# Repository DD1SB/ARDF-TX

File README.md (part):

# ARDF-TX

**Hardware evaluation stage — physical transmitter qualification pending.**

ARDF-TX is a modular open-source transmitter platform for Amateur Radio Direction
Finding (ARDF), with separate 80 m and 2 m RF boards and a common ESP32-S3
controller. Its goals are affordable reproduction, ordinary PCB manufacturing,
autonomous contest timing, optional remote operation and explicit hardware
transmitter interlocks.

**Mini80-SMD is a fourth, independent transmitter family:** a standalone,
low-power 80 m board with its own AVR firmware and protected 1S battery. Its
35 × 35 mm evaluation design operates without the ESP32 controller. Mini80's
sources and manufacturing review are published on `mini80-smd-evaluation`; the
Mini80 links below are pinned to the published review commit so they also work
from `main`, where the experimental hardware files are not included.

The repository contains editable KiCad sources, development history, engineering
decisions, population BOMs, verification tools and revision-specific fabrication
data. The RF designs and M6-L2 controller have independent CAD reviews. The fresh
[M6-L2 final reproduction](docs/M6_L2_FINAL_REPRODUCTION.md) supports **GO for five
controlled bare controller evaluation boards**. Physical qualification and release
for operation remain pending. No PCB has been ordered or tested.

The current RF2M revision is **M5B-E6R2**, with carrier-keyed A2A,
one shared heatsink and instrumented bring-up access. Independent engineering
review found no concrete blocker for **five bare evaluation PCBs**. See the
[E6R2 decision](docs/M5B_E6R2_REVIEW_DECISION.md) and
[final reproduction](docs/M5B_E6R2_FINAL_PUBLICATION.md). Physical RF, thermal
and operational qualification remains **NOT_RUN**. The earlier
[E6](docs/M5B_E6_REVIEW_DECISION.md) and
[E6R1](docs/M5B_E6R1_REVIEW_DECISION.md) HOLD studies remain preserved evidence.
Controller M6-L2 and RF80 are unchanged. No board or stencil has been ordered.

## Hardware architecture

| Module | Current candidate / source commit | PCB | Main functions | Native KiCad project | Engineering review |
| --- | --- | --- | --- | --- | --- |
| Common controller | **M6-L2 — ESP32 external antenna, FoxPro2 compatibility and optional GPIO expansion** / [`89f5a7d`](https://github.com/DD1SB/ARDF-TX/commit/89f5a7df6ccb4dec8fcea10e7c810a9981342ce4); previous baseline [`d94dabd`](https://github.com/DD1SB/ARDF-TX/commit/d94dabd0e40137dc44b2bb94f3707ad4636ca65f) | 100 × 100 mm | External-antenna ESP32-S3, RTC, USB-C, optional LoRa/FoxPro2/GPIO expansion and default-off interlocks | [CTRL.kicad_pro](hardware/controller/CTRL.kicad_pro) | [M6-L2](hardware/controller/review/M6-L2/README.md), previous [M6-L1](hardware/controller/review/M6-L1/README.md) |
| 80 m RF | M4A-V1R1 / [`f86684b`](https://github.com/DD1SB/ARDF-TX/commit/f86684b9ef45eec3ca4ce52edcb62896a847f1d7) | 150 × 110 mm | Si5351, LM5134B, IRF610, Classic/Sprint profiles and independent Foxoring output | [RF80_V1.kicad_pro](hardware/80m/production/RF80_V1.kicad_pro) | [M4A-V1R1](hardware/80m/production/review/M4A-V1R1/README.md) |
| 2 m RF | **M5B-E6R2 — reviewed evaluation candidate** / [`2fff321`](https://github.com/DD1SB/ARDF-TX/commit/2fff32131dd0f7da3c46fef47c04713a55df89d8); historical E5 / [`3b84366`](https://github.com/DD1SB/ARDF-TX/commit/3b84366caa985fac67fbdfbb60c4ede751b3a13e) | 150 × 110 mm | Carrier-keyed A2A, Si5351, PHA-1+, PD54008L-E, unified cooling and independent training output | [RF2M.kicad_pro](hardware/2m/RF2M.kicad_pro) | [E6R2](hardware/2m/review/M5B-E6R2/README.md); preserved [E5](hardware/2m/review/M5B-E5/README.md) |
| Standalone 80 m Mini80 | **M80-E1 hardware / M80-E2 bare-board review** / [hardware `bdac015`][mini80-e1-commit], [review `2bf55b5`][mini80-e2-commit] | **35 × 35 mm**, two layers | ATtiny1616-MNR, Si5351A-B-GT, 74HCT240PW; autonomous MINI50 training / FOX10 candidate; independent battery and fixture | [Mini80.kicad_pro][mini80-project] | [M80-E2: GO for five bare evaluation PCBs][mini80-review] |

The RF80 and RF2M boards share a **140 × 100 mm four-point M3 mounting pattern**.
The controller mounts independently and connects through short keyed IDC cables:
16 pins for RF80, 20 pins for RF2M. Their interfaces must not be interchanged.
RF battery power uses separate connectors, never the IDC cable. Normally only
one band/path transmits at a time.

The common footprint does not establish a qualified enclosure or three-board
stack. Cooling, controller antenna clearance and cable access are described in
the [historical common-enclosure study](docs/M5B_E5_COMMON_ENCLOSURE.md) and
[E6R2 mechanical assembly](docs/M5B_E6R2_MECHANICAL_ASSEMBLY.md). E6R2 places its
cooler below the board, with a protected carrier and independent supports. A
stack with both RF modules remains a physical qualification item.

Mini80 uses its own battery, two M2 mounting holes and six-pad bottom-side pogo
interface. It does not use the shared ESP32 controller, either IDC interface or
the RF80/RF2M mounting pattern.

## Intended operating modes

| Band | Intended modes |
| --- | --- |
| 80 m RF80 | Classic, Sprint, and Foxoring through a separate nominal 10 mW path |
| 2 m RF2M | Classic with genuine sinusoidal A2A amplitude modulation, and an independent very-low-power training path |
| Standalone 80 m Mini80 | Informal Sprint/training with MINI50; continuous FOX10 Foxoring candidate pending calibration and field verification |

For the controller/RF80/RF2M system, the controller contract supports configurable
schedules, Morse identification, Sprint slow/fast groups and spectator/finish-beacon
roles. Simultaneous Sprint
groups operate across a fleet; one station executes its assigned role.
Frequencies and operating profiles are configurable. Continuous beacons need
their own power/endurance model.

RF power, 70–80% AM, ERP and 12 h full / 24 h reduced-power endurance remain
**targets requiring measurement**. Antenna/feed gain, legal frequencies/power
and country/operator authorization must be established separately. IARU event
rules do not grant permission to transmit.

## Standalone 80 m Mini80 transmitter

[Mini80-SMD][mini80-readme] is an autonomous **35 × 35 mm, two-layer** low-power
80 m transmitter inspired by DF1FO's 80mSprintTX. An **ATtiny1616-MNR** controls
the **Si5351A-B-GT** programmable carrier source and **74HCT240PW,118** output
stage. Eight HCT outputs each have their own ballast resistor before the RF
signal is combined and passed through the output low-pass filter. A protected
**1S Li-ion/LiPo battery** supplies onboard **3.0 V logic** and a switched,
nominal 5 V RF supply. Charging is external; no charger is fitted, and the board's
protection circuitry does not replace a protected cell.

![Mini80 native KiCad mechanical rendering][mini80-render]

The rendering includes optional component envelopes; it is not a photograph of
assembled hardware or a statement that every shown matching component is fitted.

The two populations share the same PCB and firmware. Their nominal power
estimates use a **50 Ω reference load**, 3.55 MHz, a 4.95 V RF rail and assumed
HCT output resistance:

| Population | Eight ballast resistors | Calculated nominal RF power | Intended use |
| --- | --- | --- | --- |
| **MINI50** | 8 × 100 Ω | **47.4 mW into 50 Ω** | Informal Sprint/training only; below the official Sprint 0.3–1 W output requirement and not competition-compliant Sprint output |
| **FOX10** | 8 × 560 Ω | **10.16 mW into 50 Ω** | Foxoring candidate pending conducted-power calibration, real-antenna tuning and field verification |

Optional antenna matching populations provide impedance transformation and
selectable loading for wire training antennas. A short Foxoring antenna needs
its own selected coupling/matching setup; one population is not assumed optimal
for both. The FOX10 first-article bench population bypasses the optional matching
bank; testing requires a characterized 50 Ω dummy load. RF power, runtime estimates and antenna
models are **calculations, not physical measurements**. Adjusting conducted
power alone does not establish the required Foxoring field range.

One universal AVR firmware image supports per-unit settings for carrier
frequencies from **3.510–3.600 MHz**, role, Morse identifier, keying speed,
physical power profile, schedule and calibration. The twelve Sprint roles are
five slow and five fast transmitters, each using **MOE, MOI, MOS, MOH, MO5**,
plus spectator **S** and finish/training **MO**. Default group speeds are 10/15
WPM. The slotted roles use nominal 12-second windows in a 60-second cycle;
continuous Foxoring identifiers and independent continuous S/MO modes are also
supported. The low-power MO training role does not cover a normal-power
competition Foxoring finish beacon.

The AVR runs autonomous scheduling, Morse generation, separate carrier/timing
calibration and synchronized starting. Persistent configuration does not retain
an armed state; startup, invalid configuration and faults leave RF disabled.
**J2** provides UPDI programming, **3 V UART** configuration and a **3 V SYNC**
edge through six bottom-side pogo pads: GND, target V3 sense, UPDI, RX, TX and
SYNC. V3 is a programmer voltage reference, not an external power input.
Mini80 uses its own fixture protocol and **does not implement FoxPro2
compatibility**. See the [firmware and configuration instructions][mini80-firmware]
and [first-article/fixture guide][mini80-first-article].

| Engineering milestone | Published scope |
| --- | --- |
| **M80-E1**, [hardware commit `bdac015`][mini80-e1-commit] | Original native KiCad hardware and universal AVR firmware |
| **M80-E2**, [review commit `2bf55b5`][mini80-e2-commit] | Final bare-board manufacturing review; **no copper or firmware revision** |

KiCad 10 ERC/DRC, design verification and firmware host checks passed.
**GO: five unpopulated evaluation PCBs. HOLD: populated fleet release,
competition claims and operational compliance.** No Mini80 hardware has yet
been ordered or energized. Physical checks remain for HCT output skew/current,
spectrum, RF power, power consumption, frequency/timing stability, keying-envelope
behavior and FOX10 audibility at **30 m** with no audibility at **250 m**. The
[M80-E2 manufacturing review][mini80-review] records these limits and the
U2 exposed-pad solder-wicking and J2 fixture-orientation assembly risks.

Native sources: [KiCad project][mini80-project],
[schematic][mini80-schematic] and [PCB][mini80-pcb]. Start with the
[Mini80 design notes][mini80-readme], [exact order instructions][mini80-order]
and [FOX10 first-article plan][mini80-first-article].

## Controller and optional LoRa

The M6-L2 controller uses an **ESP32-S3-WROOM-1U-N4**, 4 MB flash with no PSRAM,
and an **RV-3032-C7 RTC** with
isolated CR1220 backup. USB-C provides programming, configuration, diagnostics
and time setting. Standalone operation does not require a network. The firmware
currently supplied is a hardware-contract/test foundation, not complete contest
firmware.

The ESP32's external **2.4 GHz** antenna port is separate from optional LoRa.
The optional FoxPro2 interface uses isolated population routing and protected
open-drain signalling; legacy battery reporting is unavailable for both 2S and
4S. Optional TCA9534A expansion provides eight limited 3.3 V GPIOs at address
0x38. Both options may remain completely unpopulated. The controller safety architecture
is unchanged. See the [M6-L2 review](hardware/controller/review/M6-L2/README.md)
for exact module lands, cable wiring, boot restrictions and test limitations.
Genuine FoxPro2 interoperability remains physically untested. Legacy oscillator
calibration is unsupported; test transmission requires native safety authorization
and is limited to 30 seconds. Target firmware integration remains incomplete.

| Radio population | Module | External antenna |
| --- | --- | --- |
| `NO_LORA` | U70 unpopulated | None required |
| `LORA_433` | Silicontra SX1262TR4-GC | Suitable 433 MHz antenna and U.FL pigtail |
| `LORA_868` | Silicontra SX1262TR8-GC | Suitable 868 MHz antenna and U.FL pigtail |

One PCB, footprint and RF feed support all options. The band comes from a
trusted assembly/configuration record; SX1262 chip identity cannot distinguish
the bands. Unknown/inconsistent configuration disables LoRa TX. Missing LoRa
does not prevent valid autonomous operation. See [LoRa variants](docs/M6_L1_LORA_VARIANTS.md)
and the [controller interface specification](docs/M6_C1_RF_INTERFACE.md).

Default-off hardware gating and local RF-board watchdogs inhibit transmission
during startup, reset and faults. Application progress owns the lease/heartbeat;
a continuously running PWM does not prove software health. Retuning, path
changes and faults require the documented disarm/rearm sequence.

## Power architecture

The common controller/RF80/RF2M system uses externally protected/balanced
**2S or 4S Li-ion packs**, with compatible
RF-board populations and validated pack identity. The controller's intended
input is approximately 6.0–16.8 V. This does not make every RF population
compatible with every pack. RF2M `BOOST2S`, `BUCK4S`, `TRAIN_ONLY` and RF80
`FULL`/`FOX_ONLY` have distinct population and operating restrictions.

Logic power is separate from dedicated RF battery connections. Use the specified
separately fused power harness and ground returns. USB-only configuration must
not energize a PA or backfeed a pack. Charging electronics are out of scope.

Read the [controller power contract](docs/M6_C1_POWER_AND_BATTERY.md),
[corrected pack-ID protection](docs/M6_C1R1_INPUT_PROTECTION.md),
[power architecture decision](docs/M2_POWER_ARCHITECTURE_DECISION.md) and
[ADR-0011](docs/decisions/ADR-0011-dual-voltage-power-and-endurance.md).
Their recorded acceptance statuses remain authoritative; publication does not
accept proposed decisions.

## Manufacturing data

The controller, RF80 and RF2M candidates use ordinary JLCPCB options:
**two-layer standard FR4, 1.6 mm, 1 oz copper, green mask, white legend, lead-free
HASL and ordinary plated through vias**. No special stackup, controlled-impedance service, filled/capped
vias or precision press-fit process is required. Published capability, local DFM,
supplier CAM acceptance and an actual quotation are separate evidence.

Authentic archives for **five individual bare evaluation boards** of each design:

| Module | Fabrication ZIP | Manufacturing instructions |
| --- | --- | --- |
| Controller M6-L2, GO for controlled bare evaluation | [ARDF_TX_CTRL_M6-L2_JLCPCB_5pcs_BARE.zip](hardware/controller/review/M6-L2/ARDF_TX_CTRL_M6-L2_JLCPCB_5pcs_BARE.zip) | [M6-L2](docs/M6_L2_MANUFACTURING.md), [decision](docs/M6_L2_REVIEW_DECISION.md) |
| Controller M6-L1, preserved historical baseline | [CTRL_M6-L1_JLCPCB_5boards.zip](hardware/80m/production/review/M4A-V1R1/three-board-order/CTRL_M6-L1_JLCPCB_5boards.zip) | [M6-L1](hardware/controller/review/M6-L1/MANUFACTURING.md) |
| RF80 M4A-V1R1 | [RF80-V1R1_JLCPCB_5boards.zip](hardware/80m/production/review/M4A-V1R1/fabrication/RF80-V1R1_JLCPCB_5boards.zip) | [V1R1](docs/M4A_V1R1_MANUFACTURING.md) |
| RF2M M5B-E6R2, GO for five bare evaluation PCBs | [RF2M-M5B-E6R2_JLCPCB_5boards.zip](hardware/2m/review/M5B-E6R2/fabrication/RF2M-M5B-E6R2_JLCPCB_5boards.zip) | [E6R2 manufacturing](docs/M5B_E6R2_MANUFACTURING.md), [full top stencil](hardware/2m/review/M5B-E6R2/fabrication/RF2M-M5B-E6R2_FULL_TOP_STENCIL.zip) |
| RF2M M5B-E5, preserved historical archive | [RF2M-M5B-E5_JLCPCB_5boards.zip](hardware/2m/review/M5B-E5/fabrication/RF2M-M5B-E5_JLCPCB_5boards.zip) | Historical [E5](docs/M5B_E5_MANUFACTURING.md); E6/E6R1 studies remain unchanged |
| Standalone Mini80 M80-E1, M80-E2 GO for five bare evaluation PCBs | [Mini80-M80-E1-JLCPCB-bare.zip][mini80-bare] | [M80-E2 order specification][mini80-order], [FOX10 first article][mini80-first-article] |

Mini80's separate order is **five 35 × 35 mm bare evaluation boards**, using
standard **1.6 mm FR4, two layers, 1 oz copper, ENIG, green solder mask and white
silkscreen**. Use the existing immutable **M80-E1 bare-board ZIP** linked above;
M80-E2 did not regenerate or revise it. The optional
[0.10 mm top-side stencil][mini80-stencil] matches the bench population. Assemble
**one FOX10 first article before any further population**. No filled/capped vias
or special stackup is required. This independent five-board GO does not change
the controller, RF80 or RF2M manufacturing statuses or packages.

RF2M E6R2 also includes the [mechanical STEP assembly](hardware/2m/review/M5B-E6R2/mechanical/complete-mechanical-stack.step),
[mounting drawing](hardware/2m/review/M5B-E6R2/mechanical/dimensioned-mounting.pdf),
[first-article test plan](docs/M5B_E6R2_FIRST_ARTICLE_TEST.md) and
[review/reproduction evidence](hardware/2m/review/M5B-E6R2/README.md).

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
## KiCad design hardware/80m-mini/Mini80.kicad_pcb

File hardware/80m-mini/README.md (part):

# Mini80-SMD — M80-E1 engineering candidate

**35 × 35 mm, autonomous, two-layer 80 m transmitter. GO for five unpopulated evaluation PCBs. HOLD for a populated fleet or any competition claim pending the first-article measurements.** Nothing has been ordered, programmed or energized. This independent fourth family does not change RF80 M4A-V1R1, RF2M M5B-E6R2, Controller M6-L2 or their manufacturing packages.

Open [Mini80.kicad_pro](Mini80.kicad_pro) in **KiCad 10**. The [native schematic](Mini80.kicad_sch), four subsidiary sheets, [fully routed PCB](Mini80.kicad_pcb), project symbols and custom footprints are editable CAD. The [schematic PDF](review/Mini80-schematic.pdf) and [assembly drawing](assembly/Mini80-top-assembly.pdf) support independent review.

The render shows the optional component locations as mechanical envelopes. The bench BOM leaves the loading coils and C30 unpopulated. AVR, connector and Coilcraft bodies use original simplified envelope models; these images are not photographs or detailed vendor CAD. See [top](render/Mini80-top.png) and [bottom](render/Mini80-bottom.png) views.

## Classification and scope

**MINI50 is informal Sprint/training equipment.** Its approximately 50 mW target is below the official Sprint 0.3–1 W requirement. **FOX10 is an uncalibrated Foxoring candidate:** target 10 mW conducted output at a defined 50 Ω reference port; antenna selection and field verification remain essential. Field audibility must include 30 m and exclude 250 m. A normal-power Foxoring finish transmitter requires separate hardware; use the existing RF80 family where appropriate.

The [IARU Region 1 Part B rules, 2025](https://www.iaru-r1.org/wp-content/uploads/2025/01/ARDF-Rules_B_2025.pdf) specify 3.510–3.600 MHz, frequency stability better than 50 ppm, Sprint spacing of at least 20 kHz, five successive 12-second slots and continuous S/MO beacons. Foxoring uses continuous identifiers at 8–15 WPM, 10 mW field transmitters, a 1–5 W finish beacon and at least 30 kHz separation from it. Relevant sections: S6, T2.6, FT2.6 and F27.3. These are equipment classifications, not permission to radiate; no regulatory or field compliance has been demonstrated.

## Architecture selection

| Candidate | Assessment |
|---|---|
| A: modern AVR + 74HC240 crystal oscillator/parallel stage | Lowest likely parts count and standby complexity. Four simultaneously deployed frequencies require four obtainable, appropriately specified carrier crystals and oscillator qualification. Exact small SMD crystals at the desired frequencies were not established as a practical low-volume basket. No historical price is treated as a quotation. Retain this simpler fallback if B's RF tests fail. |
| **B: ATtiny1616 + Si5351A + 74HCT240** | Selected. One board/image supports every frequency and role. The synthesizer plus 25 MHz crystal adds approximately $2.0–2.7 in observed parts prices, plus switching/decoupling and clock-on current. This is reasonable for twelve independently configurable training units. No high-power MOSFET PA is added. |

The ATtiny1616 3 × 3 mm QFN has enough pins for the timing crystal, separate RF safety controls, battery/rail measurements, UPDI and fixture UART. A smaller AVR would trade away interfaces or require multiplexing. **74HCT240PW,118 TSSOP20** replaces the initially considered BQ package: its cut-tape price/stock and assembly access were better. The PCB still meets the size objective. All eight outputs have separate ballast resistors; they are never connected directly together.

Main parts and sourcing observations accessed 2026-10-21:

| Reference | Exact part | Function / low-volume source |
|---|---|---|
| U3 | ATTINY1616-MNR | Autonomous controller; Mouser, MOQ 1 |
| U4 | SI5351A-B-GT | Blank MSOP10 programmable source; DigiKey, MOQ 1. Do not substitute a preprogrammed `-Bxxxxx` SKU. |
| U5 | 74HCT240PW,118 | TTL-input RF driver; Mouser, MOQ 1 |
| U2 | TPS61099DRVR | Switched boost with true disconnect; LCSC C2842395 |
| U1 | MCP1700T-3002E/TT | Always-on 3.0 V LDO; LCSC C62244 |
| Y1 | ABS07-32.768KHZ-T | 12.5 pF timing crystal; Mouser |
| Y2 | CX3225FB25000F0FZZH1 | 25 MHz, 10 pF carrier reference; Mouser |
| L20–23 | Coilcraft 1008LS-102/332XJRC | RF filter coils; Mouser/direct |
| L31, L34 | Coilcraft 1812LS-333/153XJRC | Optional antenna loading; larger packages justified by loss/SRF |

See [sourcing and costs](SOURCING.md), exact [MINI50 BOM](assembly/MINI50-bench-BOM.csv), [FOX10 BOM](assembly/FOX10-bench-BOM.csv) and [initial wire-antenna BOM](assembly/MINI50-wire-initial-BOM.csv). Catalog observations are not reserved stock. Long-tail passive prices remain explicit allowances, so this is not a fully quoted procurement release.

## Supply, safety and mechanics

A **protected 1S Li-ion/LiPo cell**, externally charged, supplies J1 pin 1 positive / pin 2 ground. The PH2 battery plug is keyed; harness polarity must be checked because commercial packs differ. F1 is a 200 mA PPTC, Q1 provides reversed-battery blocking. Neither substitutes for cell protection. The software stops below 3.2 V and requires at least 3.4 V to re-arm. Configure the AVR BOD to 2.9 V. The converter's own low-voltage limit is not suitable cell protection.

MCP1700 makes 3.0 V logic. The boost feedback 390 kΩ/100 kΩ gives about 4.9 V in PWM and 5.05 V in PFM; a 4.6–5.35 V firmware rail window catches major faults. Both BOOST_EN and the switched clock supply default off in hardware. TPS61099 true output disconnect avoids an always-live battery-through-inductor RF supply. Preparation allows 12 ms for boost, 10 ms for clock supply, then bounded oscillator/PLL settling. These delays require measurement.

The Si5351 output high level is compatible with HCT's 2 V TTL threshold at its nominal powered rail. A shared 1 kΩ clock resistor limits input clamp current while the HCT supply is off. Its RC delay with eight inputs can distort duty cycle and must be checked. Q6 controls both output enables; retuning inhibits RF and removes VPA first. R21 pulls OE_N to **VPA**, avoiding a separate-rail backfeed path. RF, envelope, clock and boost controls all start low.

Q4/Q5 provide a supply envelope using 100 kΩ/100 kΩ and 47 nF: nominal gate time constants 2.35/4.7 ms. The firmware permits a 15.625 ms decay tail before inhibiting the clock. RF amplitude follows the actual transistor/load behavior; operation below the HCT guaranteed supply range during transitions needs testing. Immediate fault shutdown takes priority over a smooth tail.

The outline is **35 × 35 mm**, FR4, 1.6 mm, two layers, 1 oz copper. No impedance-controlled stackup. Two 2.2 mm NPTH holes at relative (2.5,2.5) and (32.5,32.5) accept M2 nylon hardware. Keep metal fixings away from the antenna network. Allow at least a 37 × 37 mm housing cavity and approximately 8 mm board/connector height, plus plug insertion, strain relief and battery space. J1's approximately 4.8 mm body is the tallest populated bench part; optional 1812 inductors are approximately 3.6 mm high. Actual cell and enclosure envelopes must be checked before selection.

Battery capacities below refer to protected packs; 150–300 mAh suits the slotted foxes, 560 mAh or larger suits S, and approximately 750–1,200 mAh suits a twelve-hour MO beacon. A 1,200–1,500 mAh pack is the calculated 24-hour FOX10 candidate. Battery and enclosure are outside the board dimensions and BOM prices. No charger is fitted.

## RF output and matching

```text
Si5351 CLK0 -> 1k -> eight HCT inputs
  eight inverted outputs -> eight individual 100R / 560R -> sum
  -> 10n C0G DC block
  -> 1u -- 3.3u -- 3.3u -- 1u -> TP7 RF50
          |        |        |
        1200p    1000p     820p
          GND      GND      GND
  -> optional series 2.2u / shunt 470p transformer
  -> selectable 33u + 10u + 4.7u + 15u loading -> ANT
CP is the RF ground/counterpoise connection.
```

The shunt capacitors follow the first, second and third series coils respectively. The diagram's columns are illustrative; use the native schematic/netlist for wiring.

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
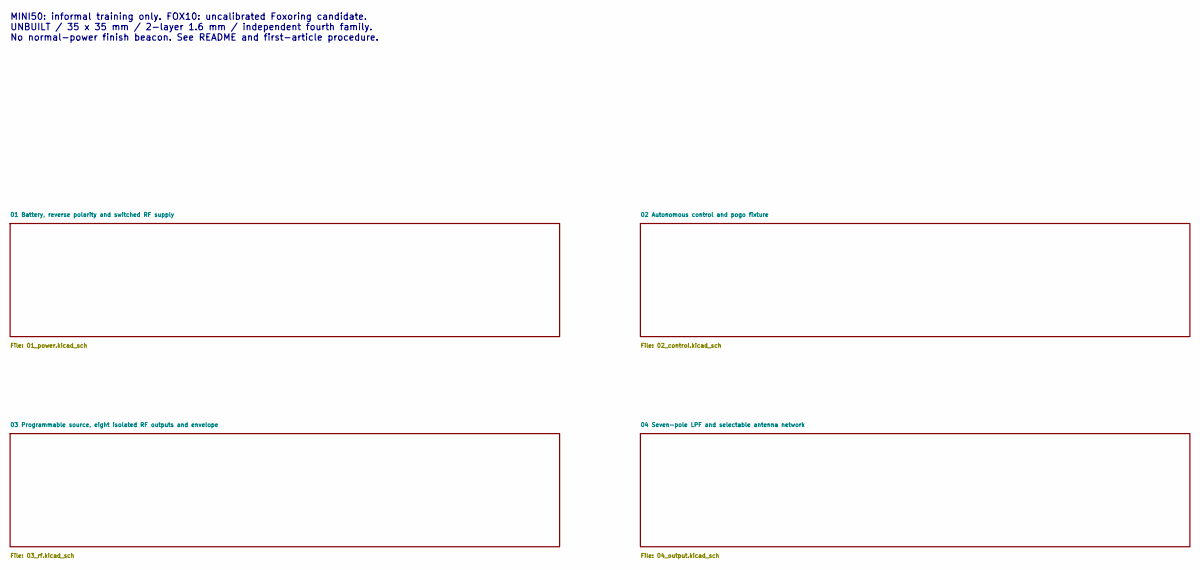
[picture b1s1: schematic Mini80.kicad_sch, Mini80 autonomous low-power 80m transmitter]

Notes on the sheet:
MINI50: informal training only. FOX10: uncalibrated Foxoring candidate. UNBUILT / 35 x 35 mm / 2-layer 1.6 mm / independent fourth family. No normal-power finish beacon. See README and first-article procedure.

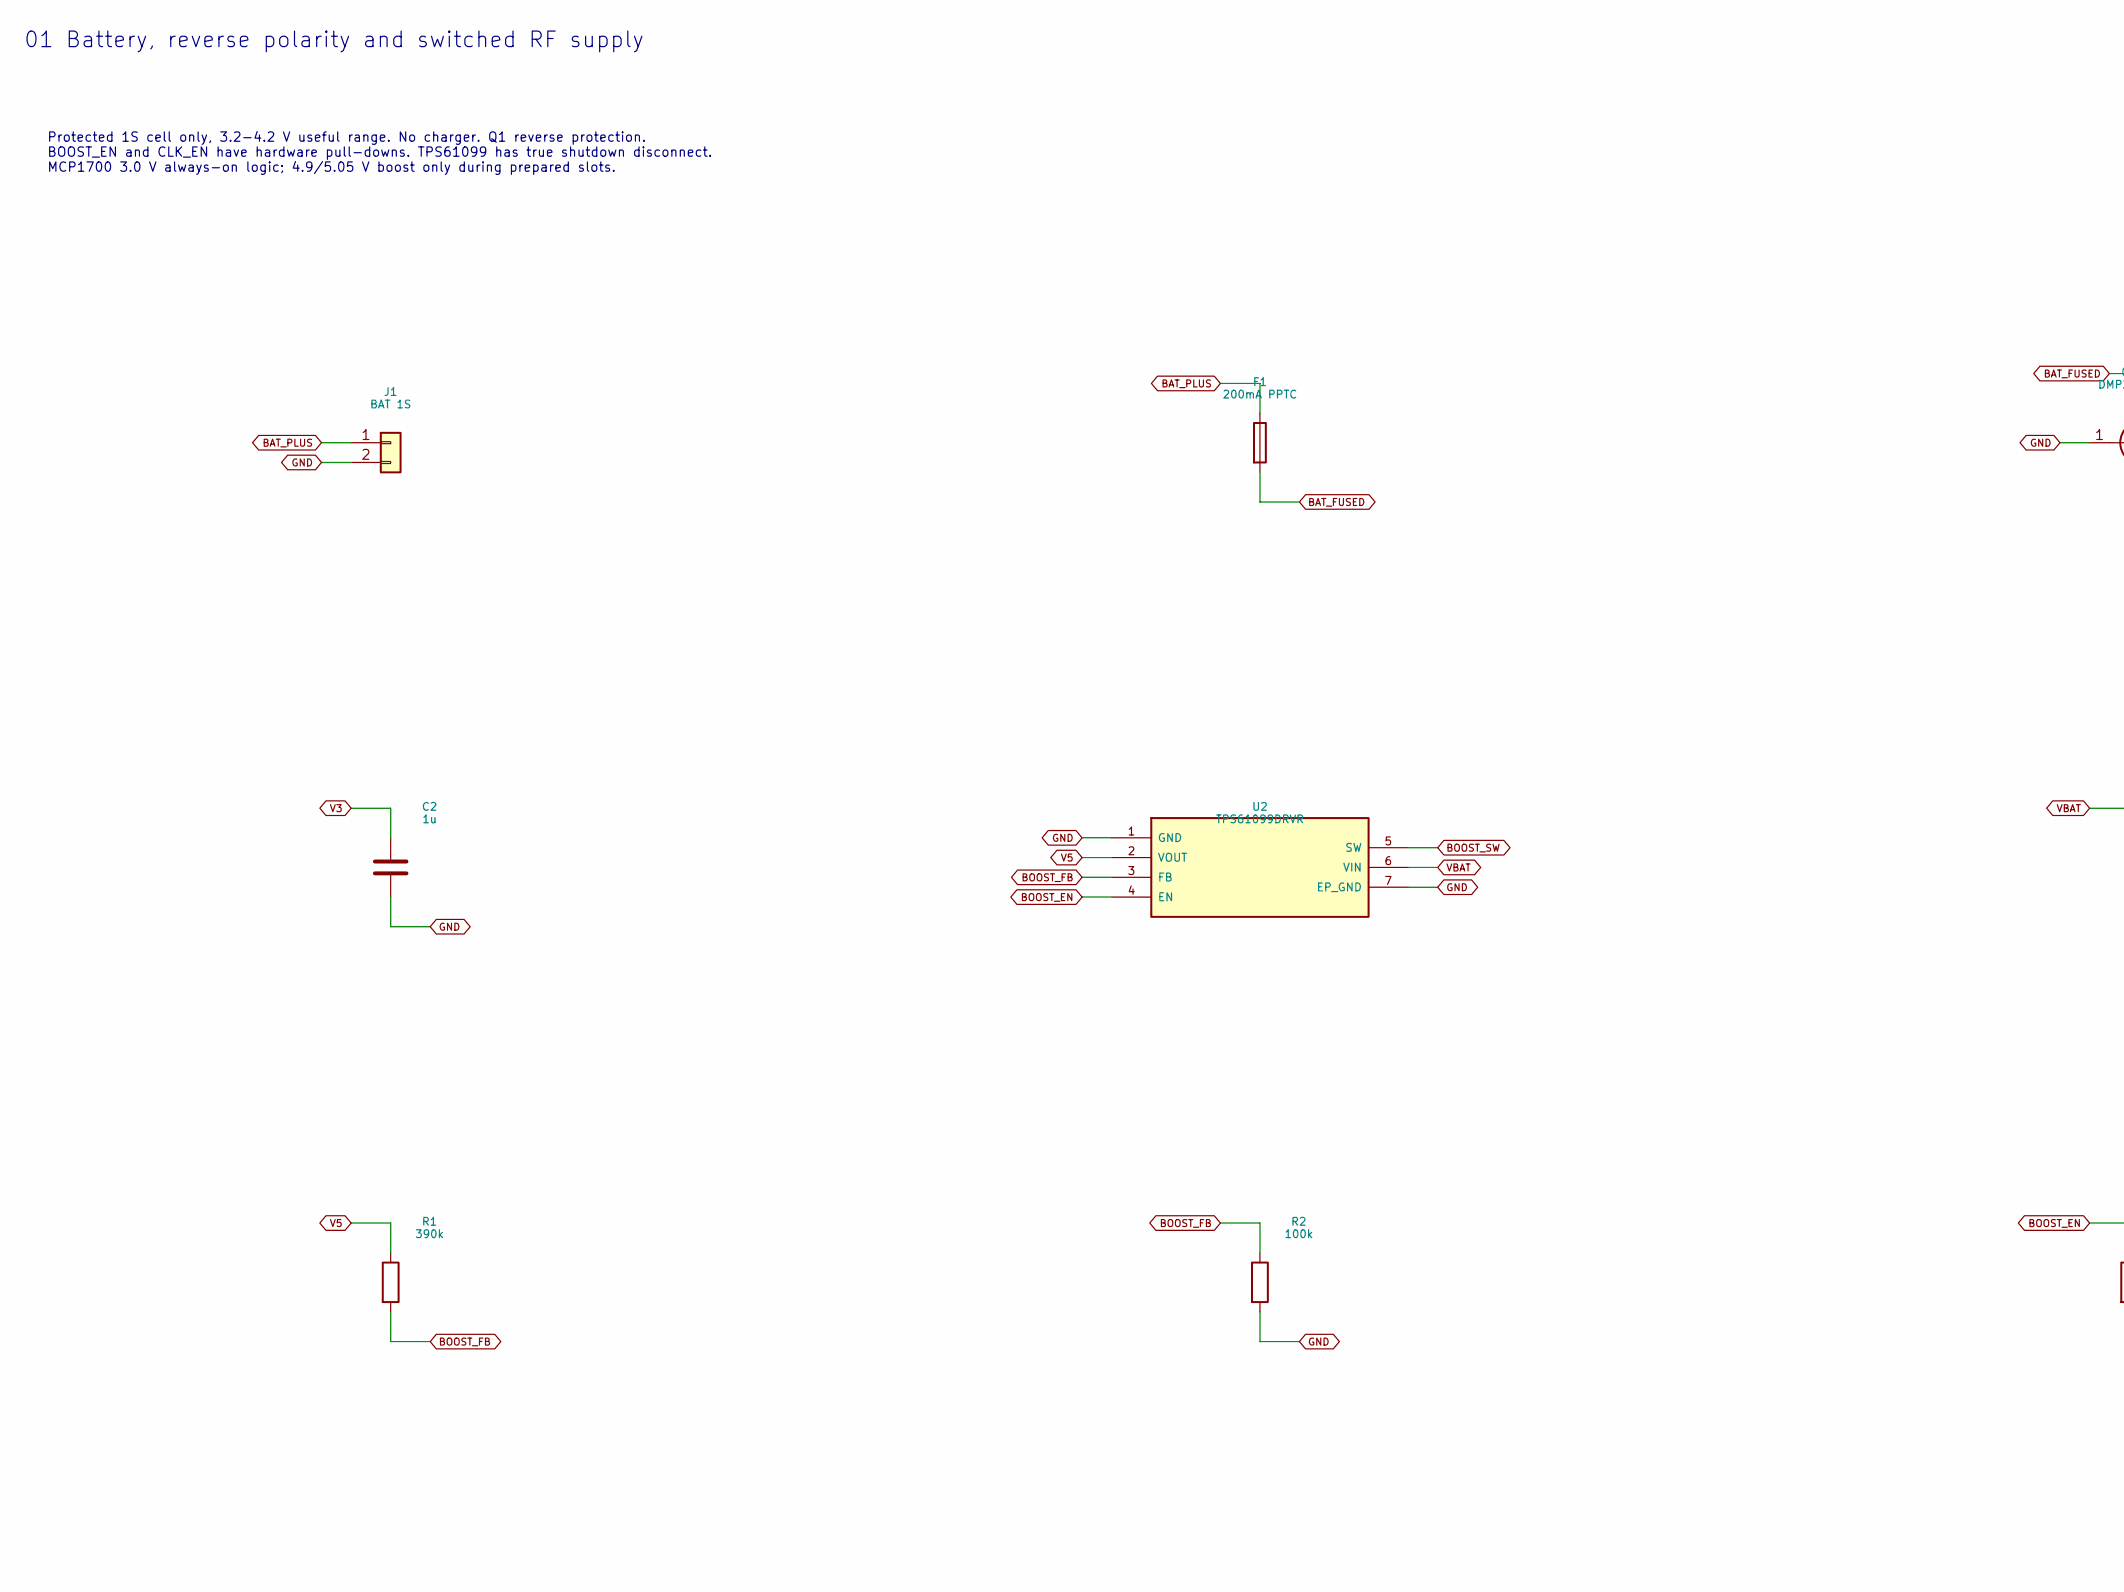
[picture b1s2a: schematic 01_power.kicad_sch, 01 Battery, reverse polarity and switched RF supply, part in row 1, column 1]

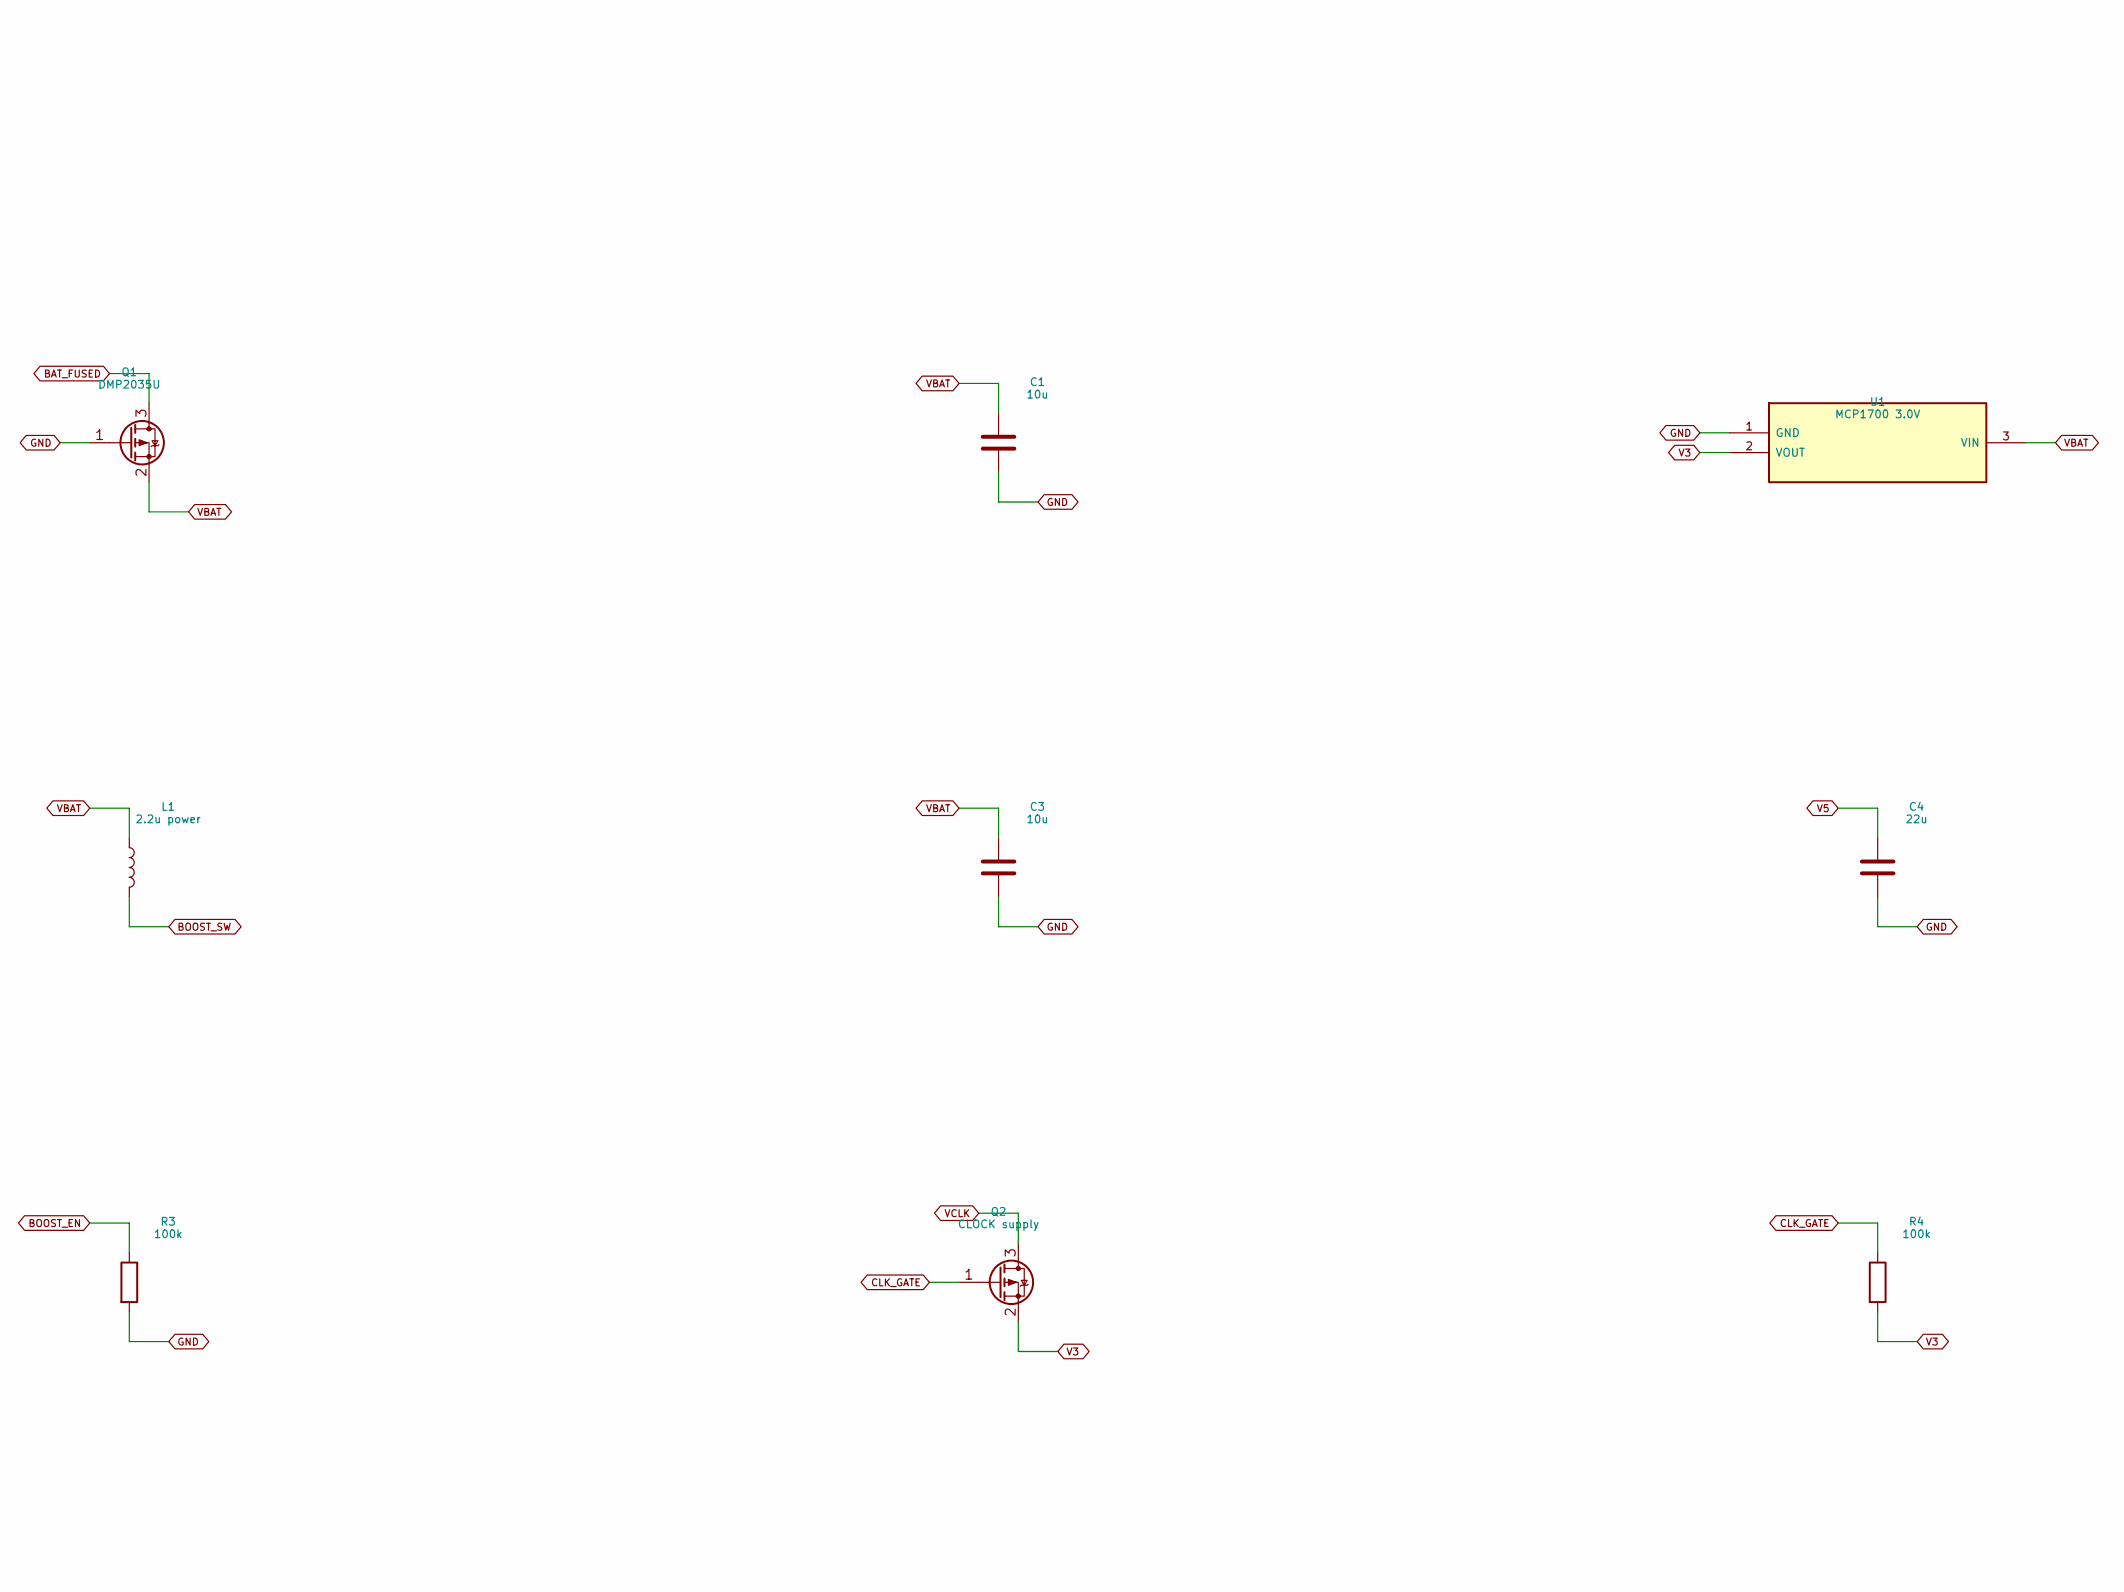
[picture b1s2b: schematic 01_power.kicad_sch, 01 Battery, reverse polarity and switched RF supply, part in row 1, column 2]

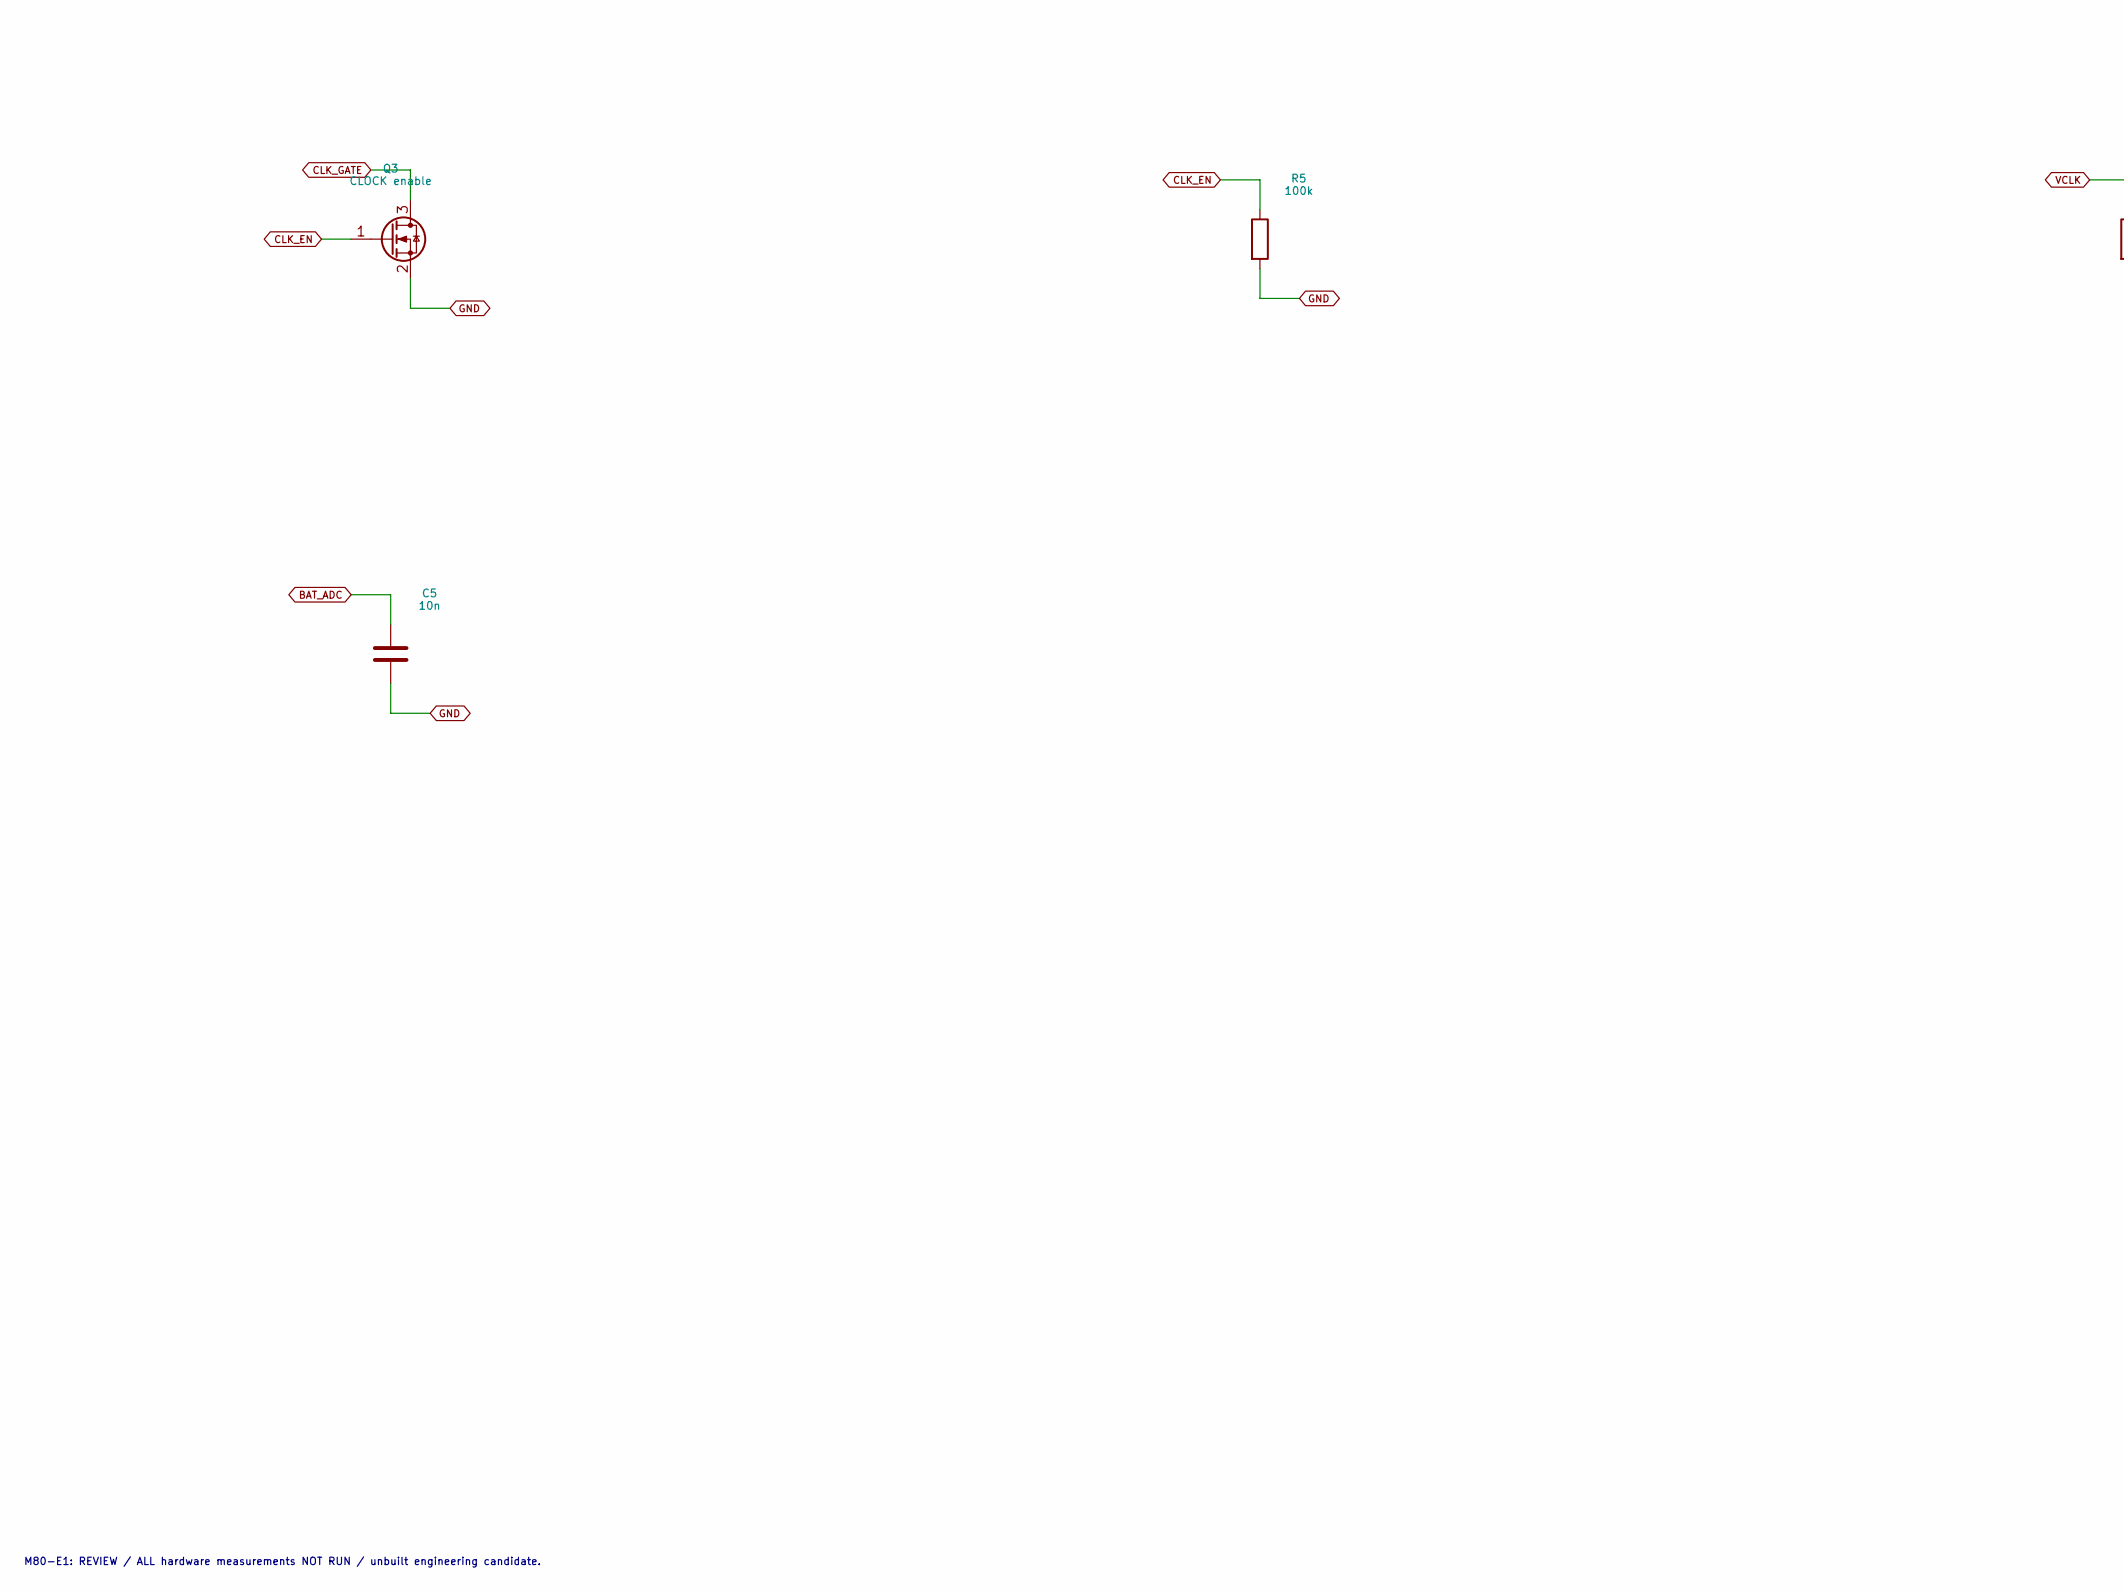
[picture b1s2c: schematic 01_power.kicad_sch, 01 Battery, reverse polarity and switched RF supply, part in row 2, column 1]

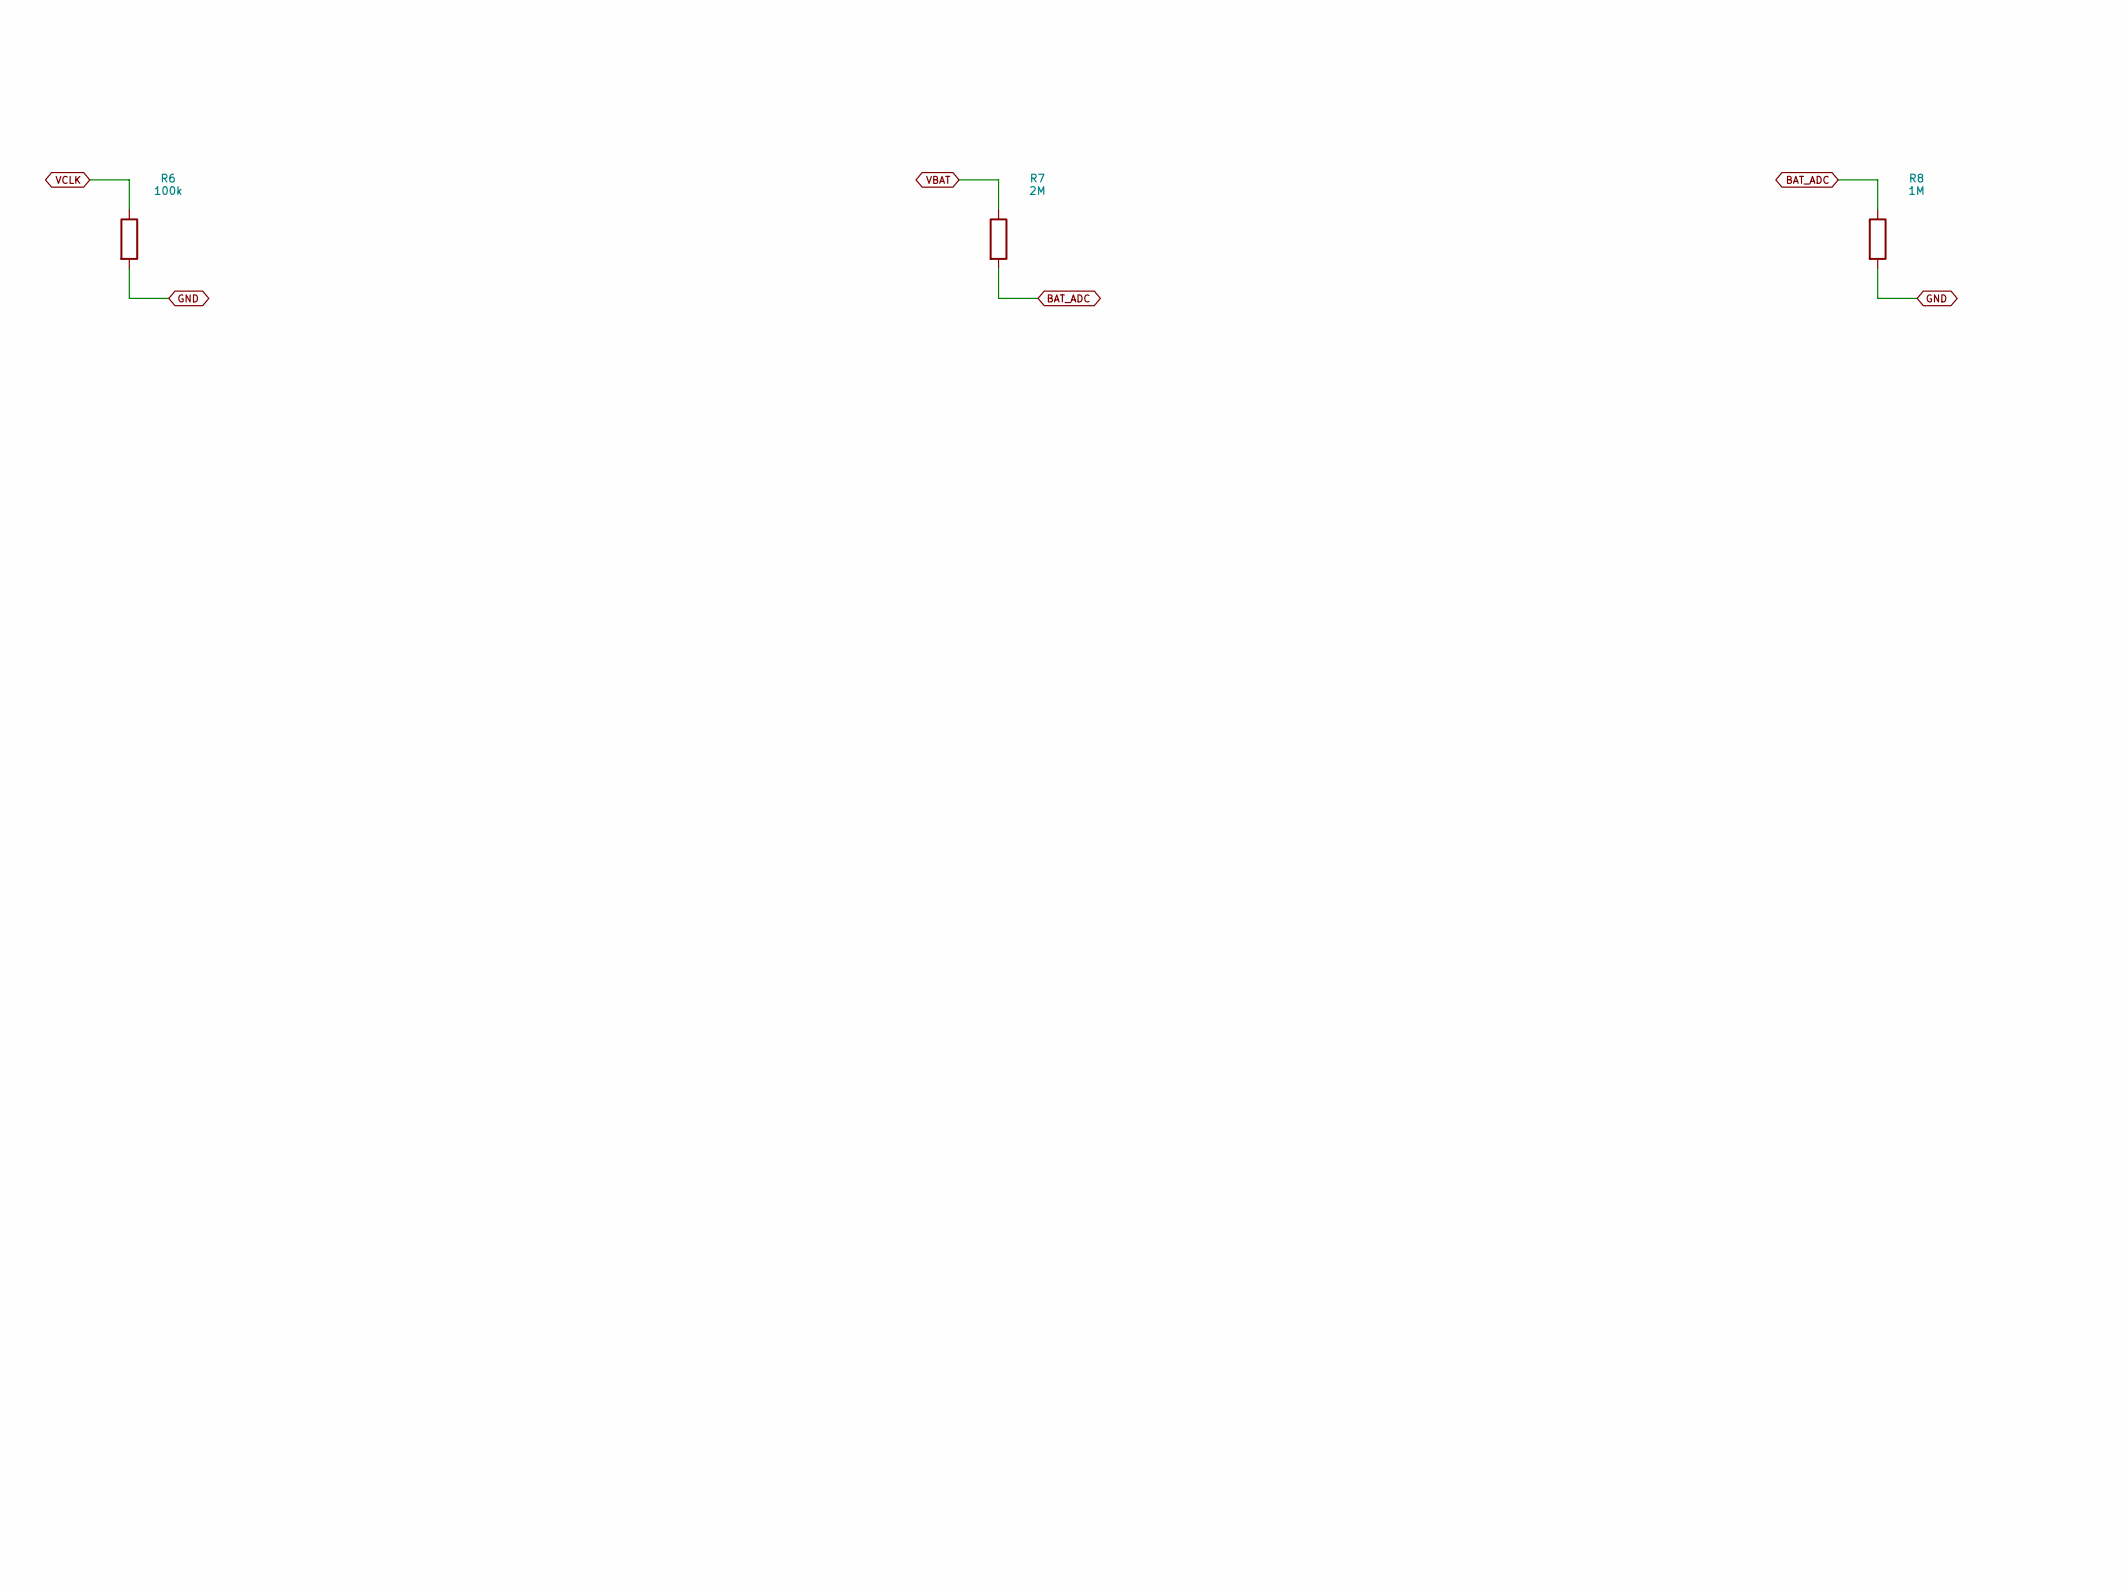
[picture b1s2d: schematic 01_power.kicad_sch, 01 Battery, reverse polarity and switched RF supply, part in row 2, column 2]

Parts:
C1, C3: 10u; C_0805_2012Metric; MPN GRM21BR61C106KE15L
C2: 1u; C_0402_1005Metric; MPN GRM155R61A105KE15D
C4: 22u; C_0805_2012Metric; MPN GRM21BR61A226ME44L
C5: 10n; C_0402_1005Metric; MPN GRM155R71H103KA88D
F1: 200mA PPTC; MF_FSMF0603; MPN MF-FSMF020X-2
J1: BAT 1S; JST_PH_S2B-PH-SM4-TB_1x02-1MP_P2.00mm_Horizontal; MPN S2B-PH-SM4-TB(LF)(SN)
L1: 2.2u power; L_Sunlord_SWPA3015S; MPN SWPA3015S2R2MT
Q1: DMP2035U; SOT-23; MPN DMP2035U-7
Q2: CLOCK supply; SOT-23; MPN DMP2035U-7
Q3: CLOCK enable; SOT-23; MPN 2N7002,215
R1: 390k; R_0402_1005Metric; MPN RC0402FR-07390KL
R2, R3, R4, R5, R6: 100k; R_0402_1005Metric; MPN RC0402FR-07100KL
R7: 2M; R_0402_1005Metric; MPN RC0402FR-072ML
R8: 1M; R_0402_1005Metric; MPN RC0402FR-071ML
U1: MCP1700 3.0V; SOT-23; MPN MCP1700T-3002E/TT
U2: TPS61099DRVR; WSON-6-1EP_2x2mm_P0.65mm_EP1x1.6mm; MPN TPS61099DRVR

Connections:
BAT_ADC: C5.1, R7.2, R8.1; also elsewhere on the board
BAT_FUSED: F1.2, Q1.3 (D)
BAT_PLUS: F1.1, J1.1
BOOST_EN: R3.1, U2.4 (EN); also elsewhere on the board
BOOST_FB: R1.2, R2.1, U2.3 (FB)
BOOST_SW: L1.2, U2.5 (SW)
CLK_EN: Q3.1 (G), R5.1; also elsewhere on the board
CLK_GATE: Q2.1 (G), Q3.3 (D), R4.1
GND: C1.2, C2.2, C3.2, C4.2, C5.2, J1.2, Q1.1 (G), Q3.2 (S), R2.2, R3.2, R5.2, R6.2, R8.2, U1.1 (GND), U2.1 (GND), U2.7 (EP_GND); also elsewhere on the board
V3: C2.1, Q2.2 (S), R4.2, U1.2 (VOUT); also elsewhere on the board
V5: C4.1, R1.1, U2.2 (VOUT); also elsewhere on the board
VBAT: C1.1, C3.1, L1.1, Q1.2 (S), R7.1, U1.3 (VIN), U2.6 (VIN); also elsewhere on the board
VCLK: Q2.3 (D), R6.1; also elsewhere on the board

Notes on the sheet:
01 Battery, reverse polarity and switched RF supply
Protected 1S cell only, 3.2-4.2 V useful range. No charger. Q1 reverse protection. BOOST_EN and CLK_EN have hardware pull-downs. TPS61099 has true shutdown disconnect. MCP1700 3.0 V always-on logic; 4.9/5.05 V boost only during prepared slots.
M80-E1: REVIEW / ALL hardware measurements NOT RUN / unbuilt engineering candidate.

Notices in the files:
README.md:
License:
Original contributor-owned firmware, tooling, documentation and KiCad design
work are under the [MIT License](LICENSE), except where separate notices apply.
MIT does not relicense third-party material.
[Third-party notices](THIRD_PARTY_NOTICES.md) cover OpenARDF MIT attribution,
KiCad-derived library data under CC-BY-SA-4.0 with its exception, and the
GPL-2.0-or-later sliver helper. Historical DL3BBX-derived M5A-R3 retains its
private-construction/commercial-permission restrictions; it is not unrestricted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
